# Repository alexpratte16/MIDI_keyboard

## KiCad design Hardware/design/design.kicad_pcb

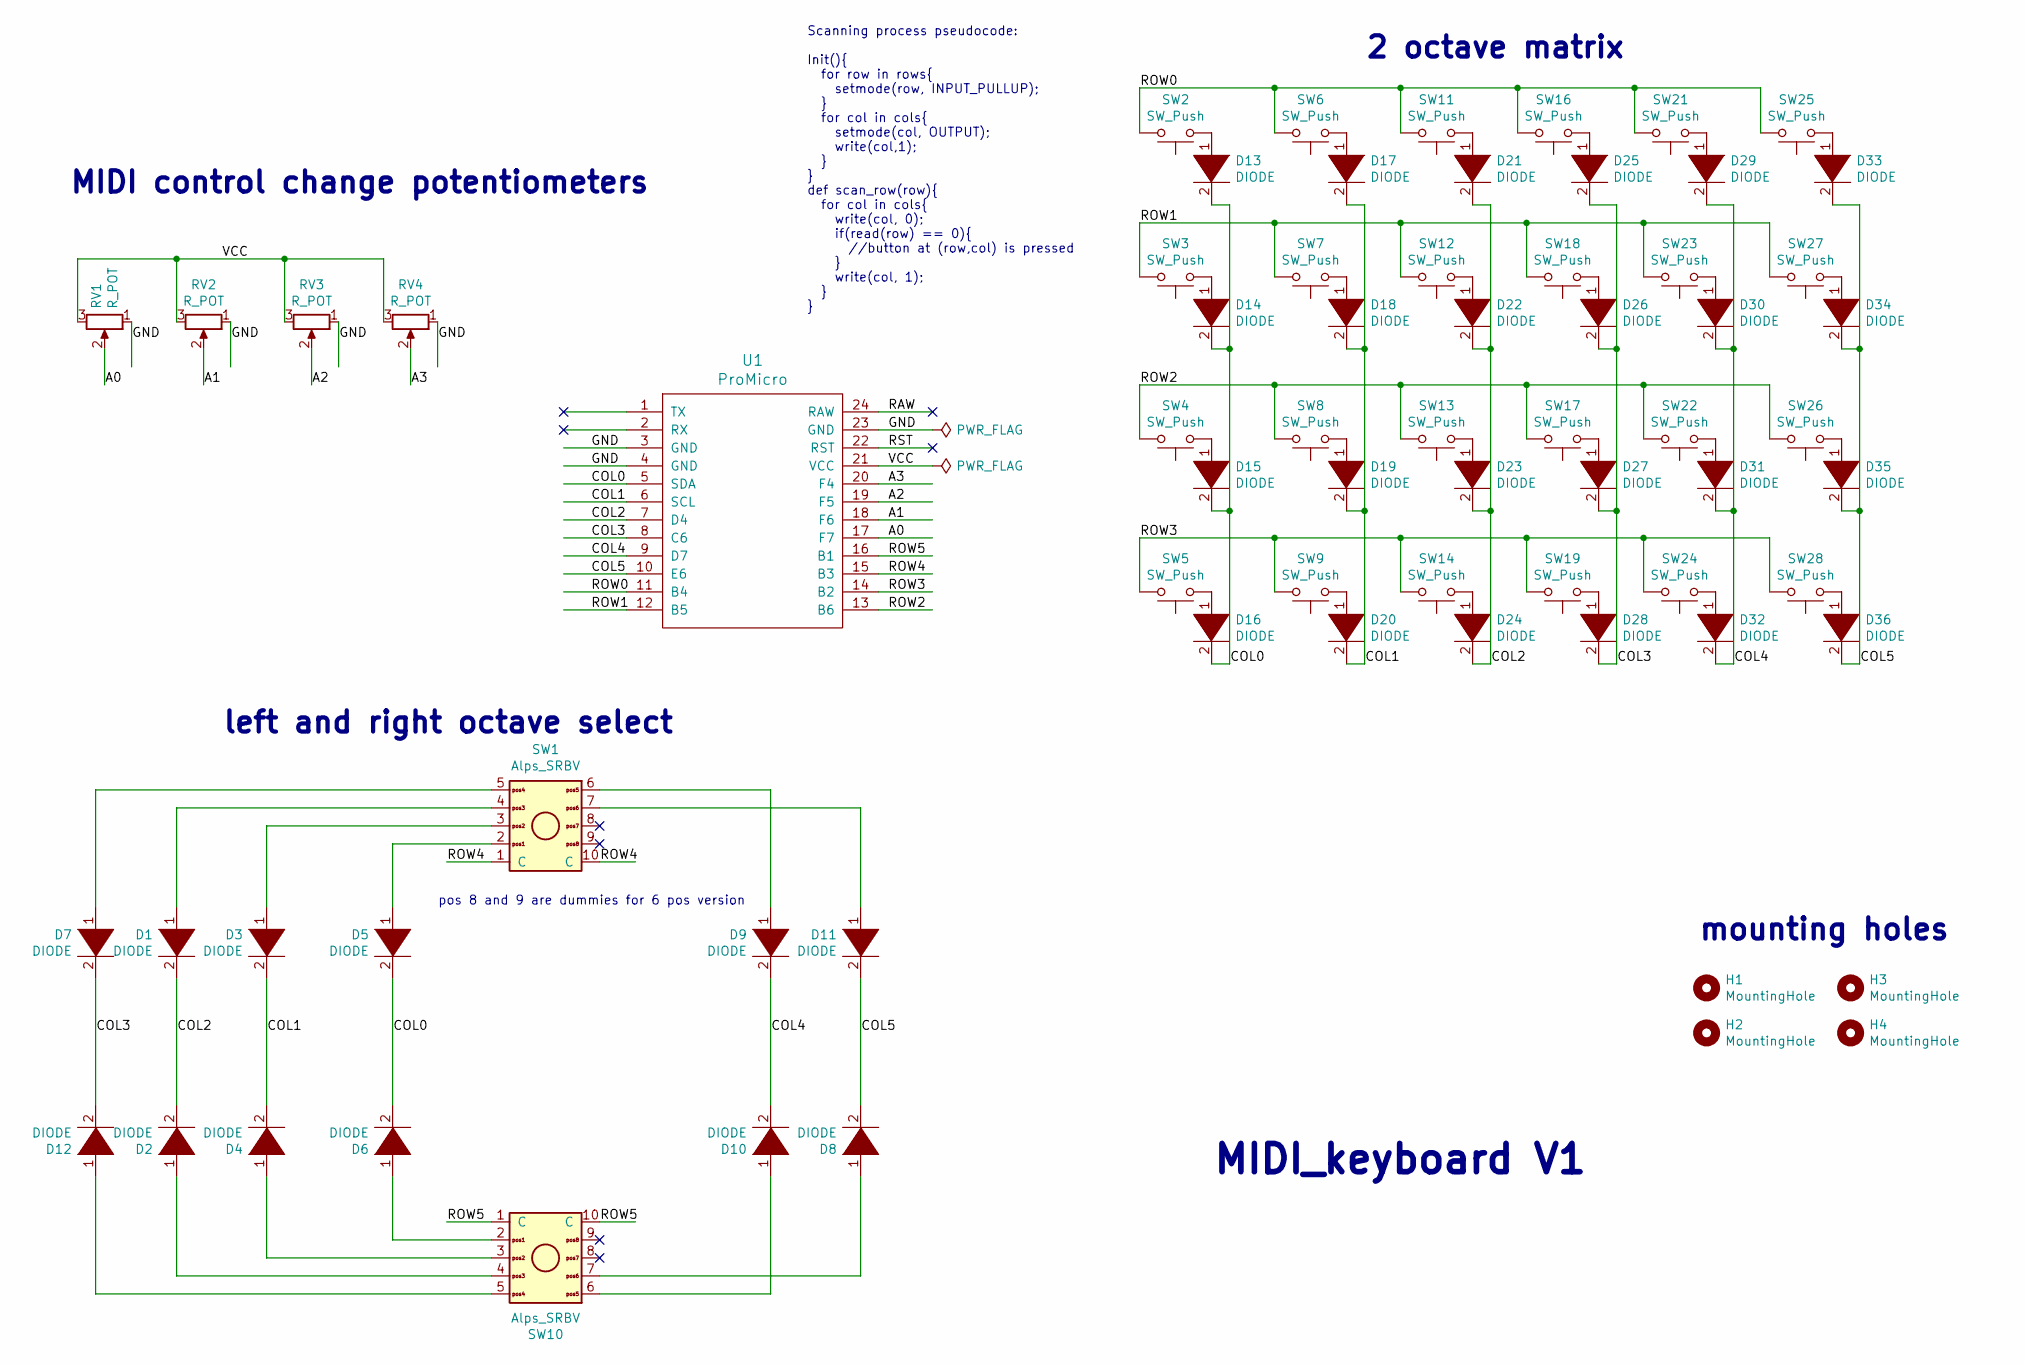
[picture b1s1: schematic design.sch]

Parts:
D1, D2, D3, D4, D5, D6, D7, D8, D9, D10, D11, D12, D13, D14, D15, D16, D17, D18, D19, D20, D21, D22, D23, D24, D25, D26, D27, D28, D29, D30, D31, D32, D33, D34, D35, D36: DIODE; D_1206_3216Metric
H1, H2, H3, H4: MountingHole; MountingHole_4mm
RV1, RV2, RV3, RV4: R_POT; Potentiometer_Bourns_PTV09A-1_Single_Vertical
SW1, SW10: Alps_SRBV; ALPS_SRBV
SW2, SW3, SW4, SW5, SW6, SW7, SW8, SW9, SW11, SW12, SW13, SW14, SW16, SW17, SW18, SW19, SW21, SW22, SW23, SW24, SW25, SW26, SW27, SW28: SW_Push; SW_Cherry_MX_1.00u_PCB
U1: ProMicro

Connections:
/A0: RV1.2, U1.17 (F7)
/A1: RV2.2, U1.18 (F6)
/A2: RV3.2, U1.19 (F5)
/A3: RV4.2, U1.20 (F4)
/COL0: D5.2 (A), D6.2 (A), D13.2 (A), D14.2 (A), D15.2 (A), D16.2 (A), U1.5 (SDA)
/COL1: D3.2 (A), D4.2 (A), D17.2 (A), D18.2 (A), D19.2 (A), D20.2 (A), U1.6 (SCL)
/COL2: D1.2 (A), D2.2 (A), D21.2 (A), D22.2 (A), D23.2 (A), D24.2 (A), U1.7 (D4)
/COL3: D7.2 (A), D12.2 (A), D25.2 (A), D26.2 (A), D27.2 (A), D28.2 (A), U1.8 (C6)
/COL4: D9.2 (A), D10.2 (A), D29.2 (A), D30.2 (A), D31.2 (A), D32.2 (A), U1.9 (D7)
/COL5: D8.2 (A), D11.2 (A), D33.2 (A), D34.2 (A), D35.2 (A), D36.2 (A), U1.10 (E6)
/GND: RV1.1, RV2.1, RV3.1, RV4.1, U1.3 (GND), U1.4 (GND), U1.23 (GND)
/ROW0: SW2.2, SW6.2, SW11.2, SW16.2, SW21.2, SW25.2, U1.11 (B4)
/ROW1: SW3.2, SW7.2, SW12.2, SW18.2, SW23.2, SW27.2, U1.12 (B5)
/ROW2: SW4.2, SW8.2, SW13.2, SW17.2, SW22.2, SW26.2, U1.13 (B6)
/ROW3: SW5.2, SW9.2, SW14.2, SW19.2, SW24.2, SW28.2, U1.14 (B2)
/ROW4: SW1.1 (C), SW1.10 (C), U1.15 (B3)
/ROW5: SW10.1 (C), SW10.10 (C), U1.16 (B1)
/VCC: RV1.3, RV2.3, RV3.3, RV4.3, U1.21 (VCC)
unnamed: D1.1 (K), SW1.4
unnamed: D2.1 (K), SW10.4
unnamed: D3.1 (K), SW1.3
unnamed: D4.1 (K), SW10.3
unnamed: D5.1 (K), SW1.2
unnamed: D6.1 (K), SW10.2
unnamed: D7.1 (K), SW1.5
unnamed: D8.1 (K), SW10.7
unnamed: D9.1 (K), SW1.6
unnamed: D10.1 (K), SW10.6
unnamed: D11.1 (K), SW1.7
unnamed: D12.1 (K), SW10.5
unnamed: D13.1 (K), SW2.1
unnamed: D14.1 (K), SW3.1
unnamed: D15.1 (K), SW4.1
unnamed: D16.1 (K), SW5.1
unnamed: D17.1 (K), SW6.1
unnamed: D18.1 (K), SW7.1
unnamed: D19.1 (K), SW8.1
unnamed: D20.1 (K), SW9.1
unnamed: D21.1 (K), SW11.1
unnamed: D22.1 (K), SW12.1
unnamed: D23.1 (K), SW13.1
unnamed: D24.1 (K), SW14.1
unnamed: D25.1 (K), SW16.1
unnamed: D26.1 (K), SW18.1
unnamed: D27.1 (K), SW17.1
unnamed: D28.1 (K), SW19.1
unnamed: D29.1 (K), SW21.1
unnamed: D30.1 (K), SW23.1
unnamed: D31.1 (K), SW22.1
unnamed: D32.1 (K), SW24.1
unnamed: D33.1 (K), SW25.1
unnamed: D34.1 (K), SW27.1
unnamed: D35.1 (K), SW26.1
unnamed: D36.1 (K), SW28.1

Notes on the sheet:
pos 8 and 9 are dummies for 6 pos version
2 octave matrix
MIDI control change potentiometers
mounting holes
left and right octave select
MIDI_keyboard V1
Scanning process pseudocode: Init(){ for row in rows{ setmode(row, INPUT_PULLUP); } for col in cols{ setmode(col, OUTPUT); write(col,1); } } def scan_row(row){ for col in cols{ write(col, 0); if(read(row) == 0){ //button at (row,col) is pressed } write(col, 1); } }

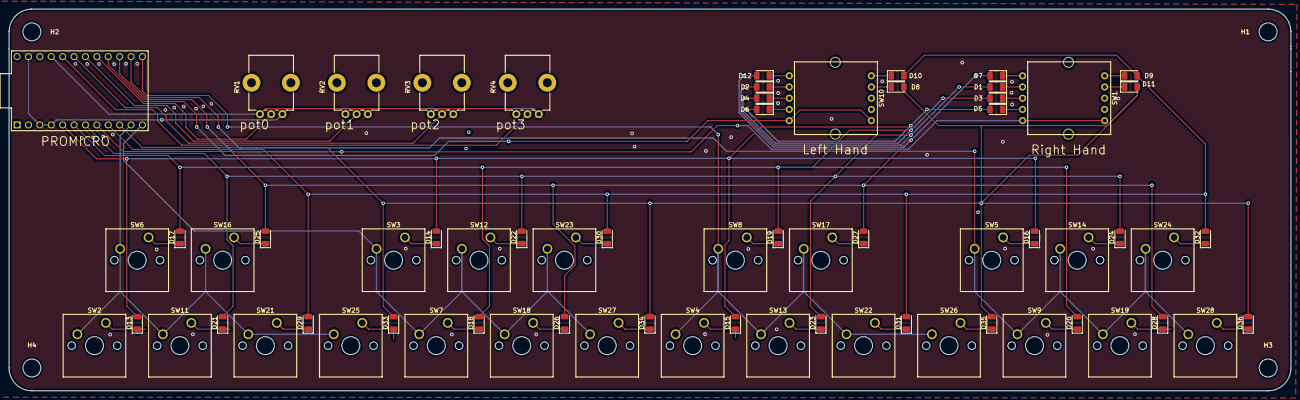
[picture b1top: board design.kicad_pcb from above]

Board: 2 copper layers, 285.8 x 85.1 mm, 71 parts (0 on the bottom side), 54 nets.

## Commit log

2021-09-21 placed most of the components on the schematic, wired pots, started on switch wiring
2021-09-21 finished layout of buttons and switches, thinking of replacing pots with sliders
2021-09-21 added test software to make sure that library is working
2021-09-21 chose and added 3 toggle switches
2021-09-21 added pseudocode in schematic so I won't forget scanning process
2021-09-23 chose rotary switches and diodes, organized layout a bit
2021-09-25 switched to 24 all cherry switches for 2 octave keyboard
2021-09-25 semi-linearized switch matrix into 2 octave layout
2021-09-25 columns routed together
2021-09-25 routed vcc and gnd for pots
2021-09-25 a less elegant solution to column routing
2021-09-25 finished column routing, sitched to 1206 SMD diodes
2021-09-25 routed all cherry switches and pots, fixed issue with rotary switch nets in schematic
2021-09-26 changed from 4x3 rotary swithches to 2x6 rotary switches for octave control of each half of keyboard
2021-09-26 added mounting holes, rounded edges and silkscreen
2021-09-26 library management
2021-09-26 fixed test file name
2021-09-27 switched COL0 and COL2 positions on the rotary switches
2021-09-27 commiting before better routing branch
2021-09-28 routing has improved
2021-09-29 board is now in production with JLCPCB
2021-09-30 software only sends MIDI packets on pin status changes
2022-05-29 Updated TODO, added some comments, removed serial.
2022-05-29 Added change control support
